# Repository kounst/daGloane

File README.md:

daGloane
========

daGloane is a quadcopter with a takeoff mass of less than 30grams

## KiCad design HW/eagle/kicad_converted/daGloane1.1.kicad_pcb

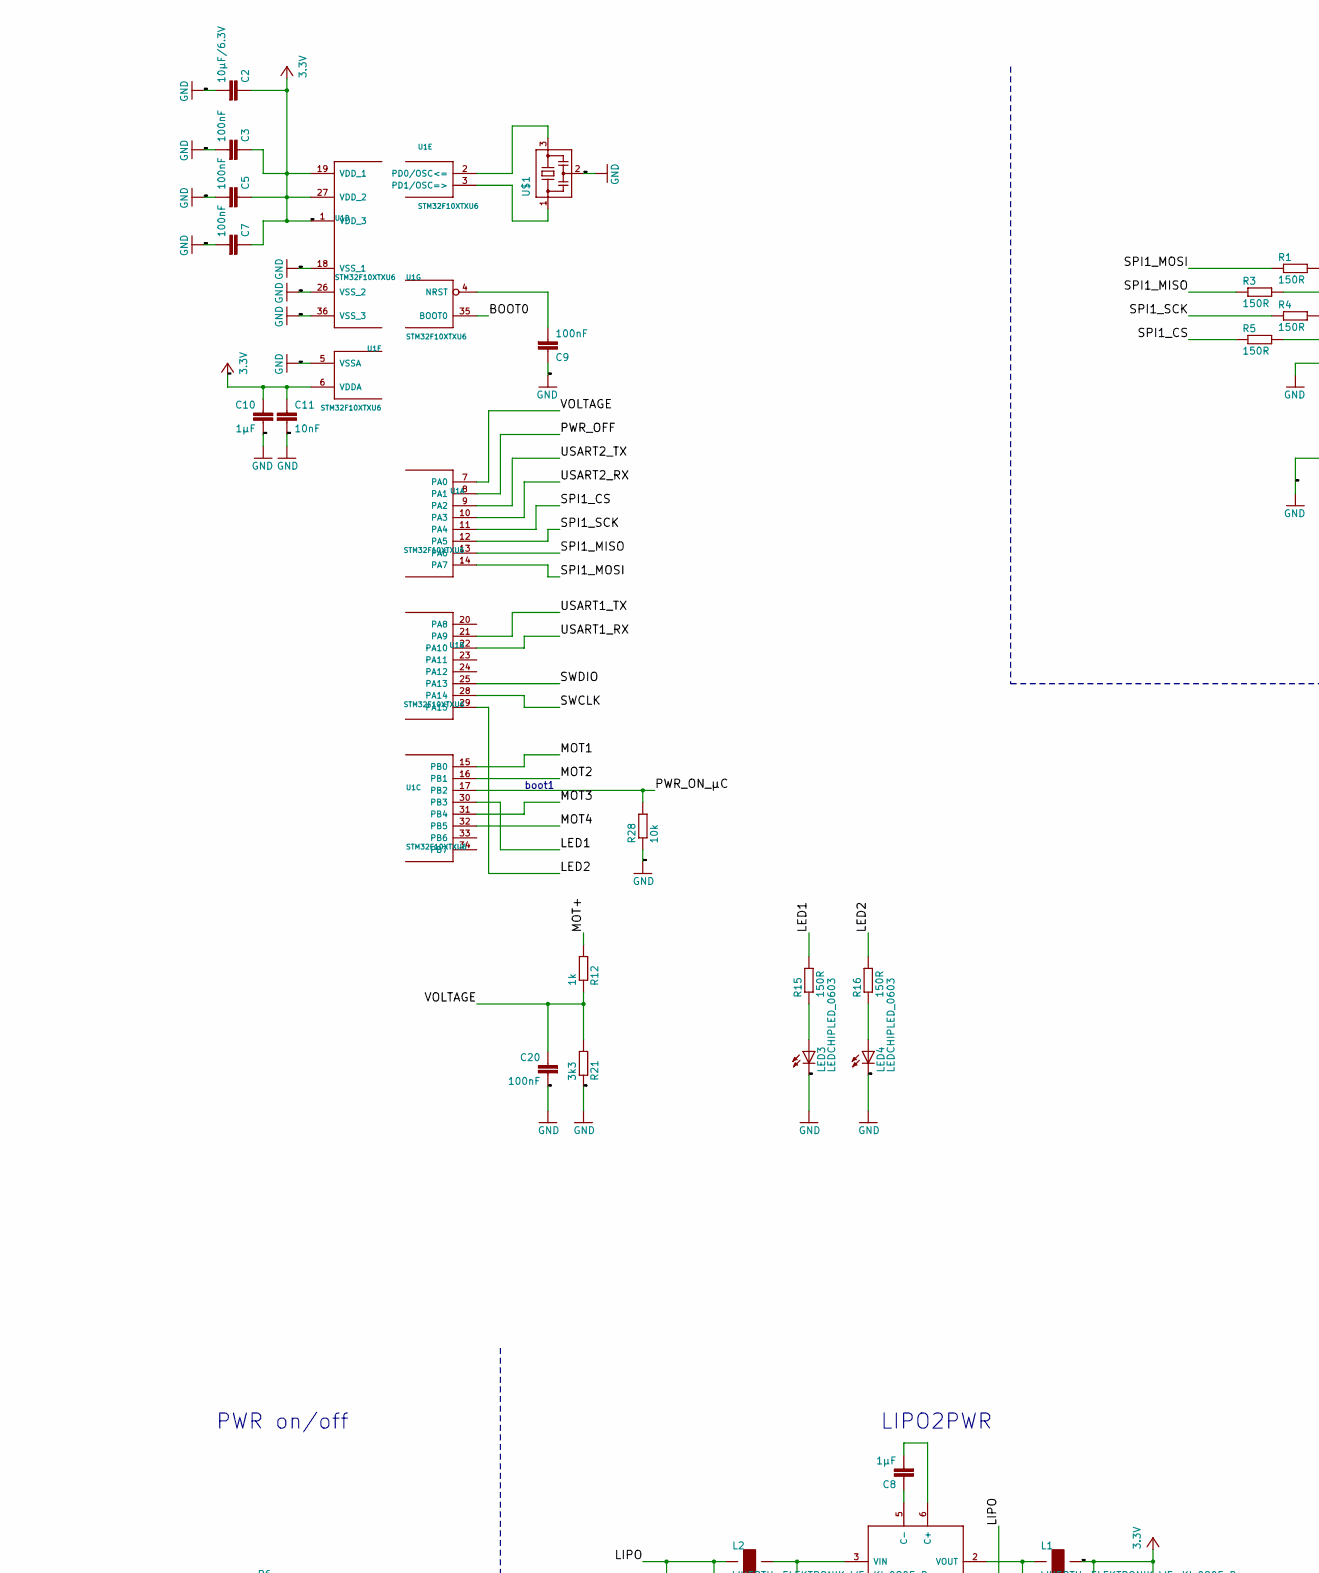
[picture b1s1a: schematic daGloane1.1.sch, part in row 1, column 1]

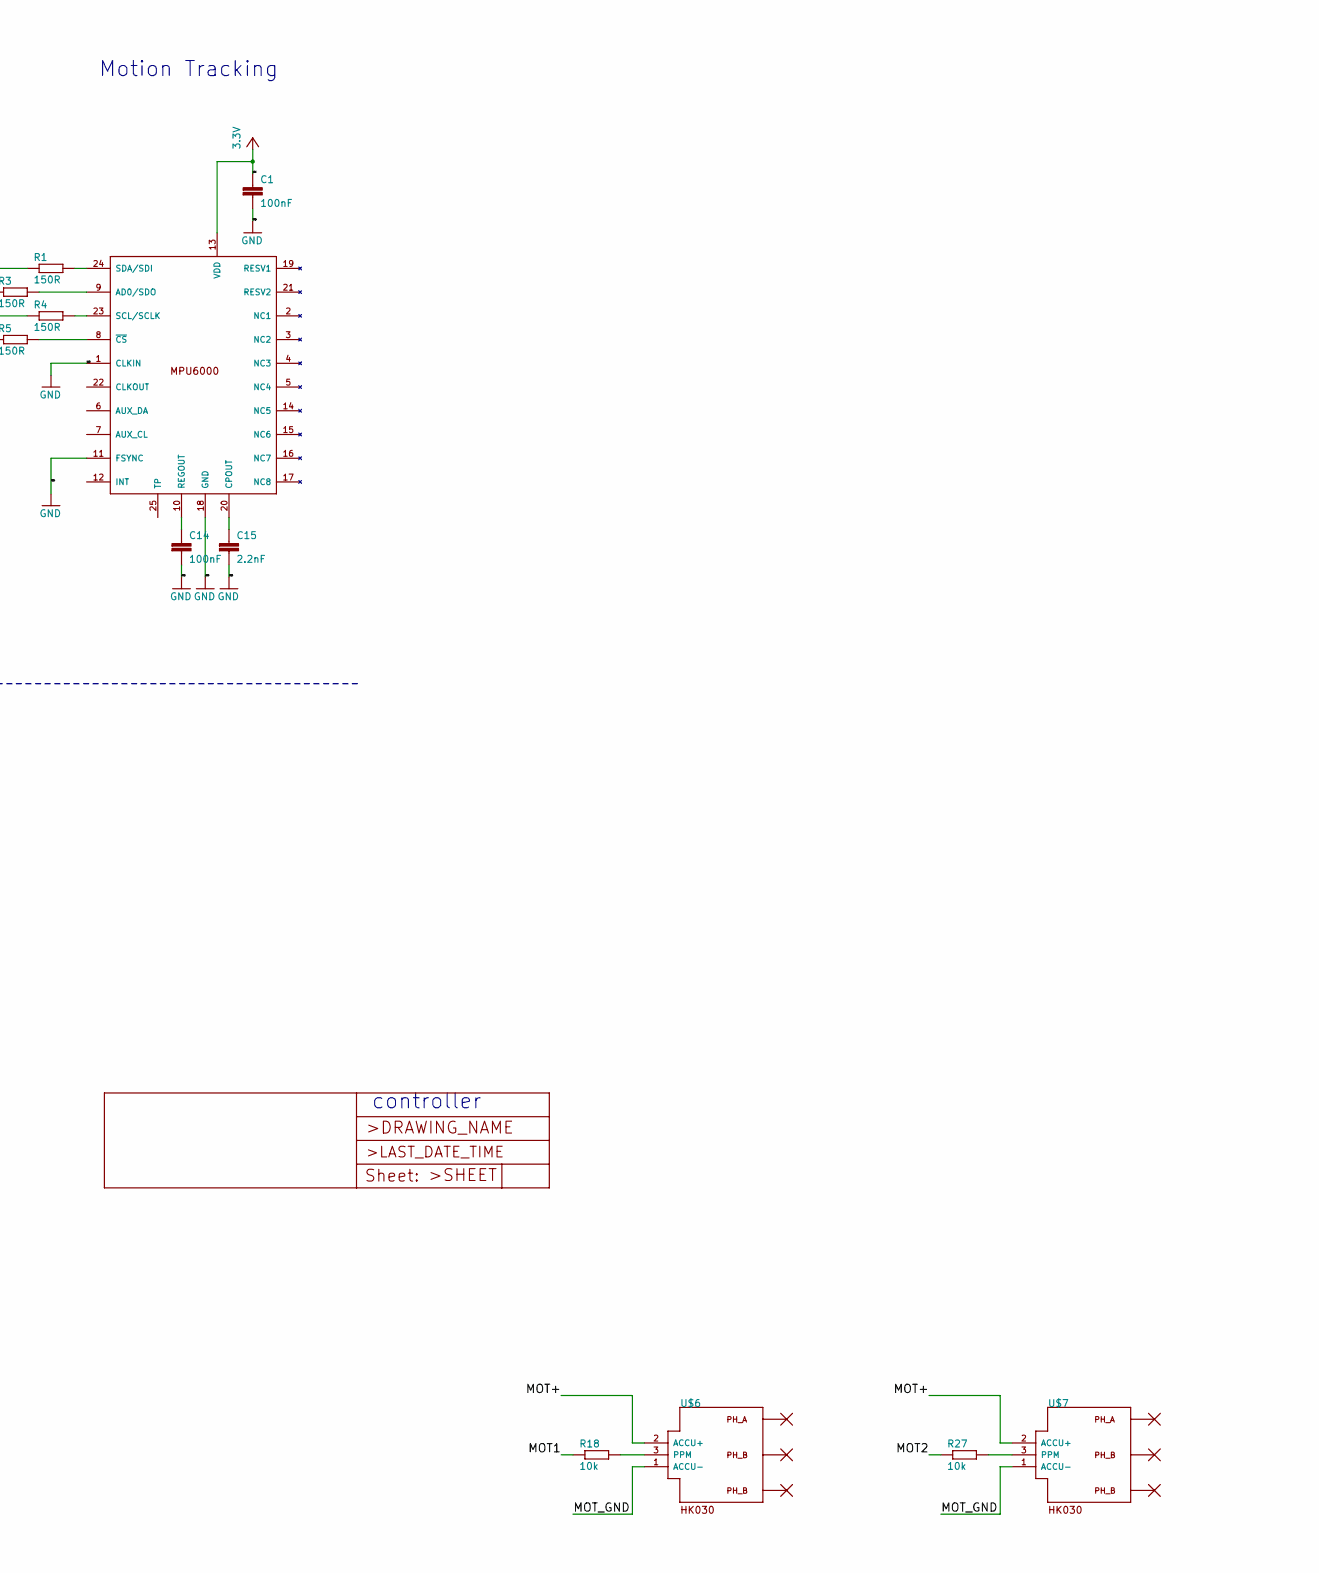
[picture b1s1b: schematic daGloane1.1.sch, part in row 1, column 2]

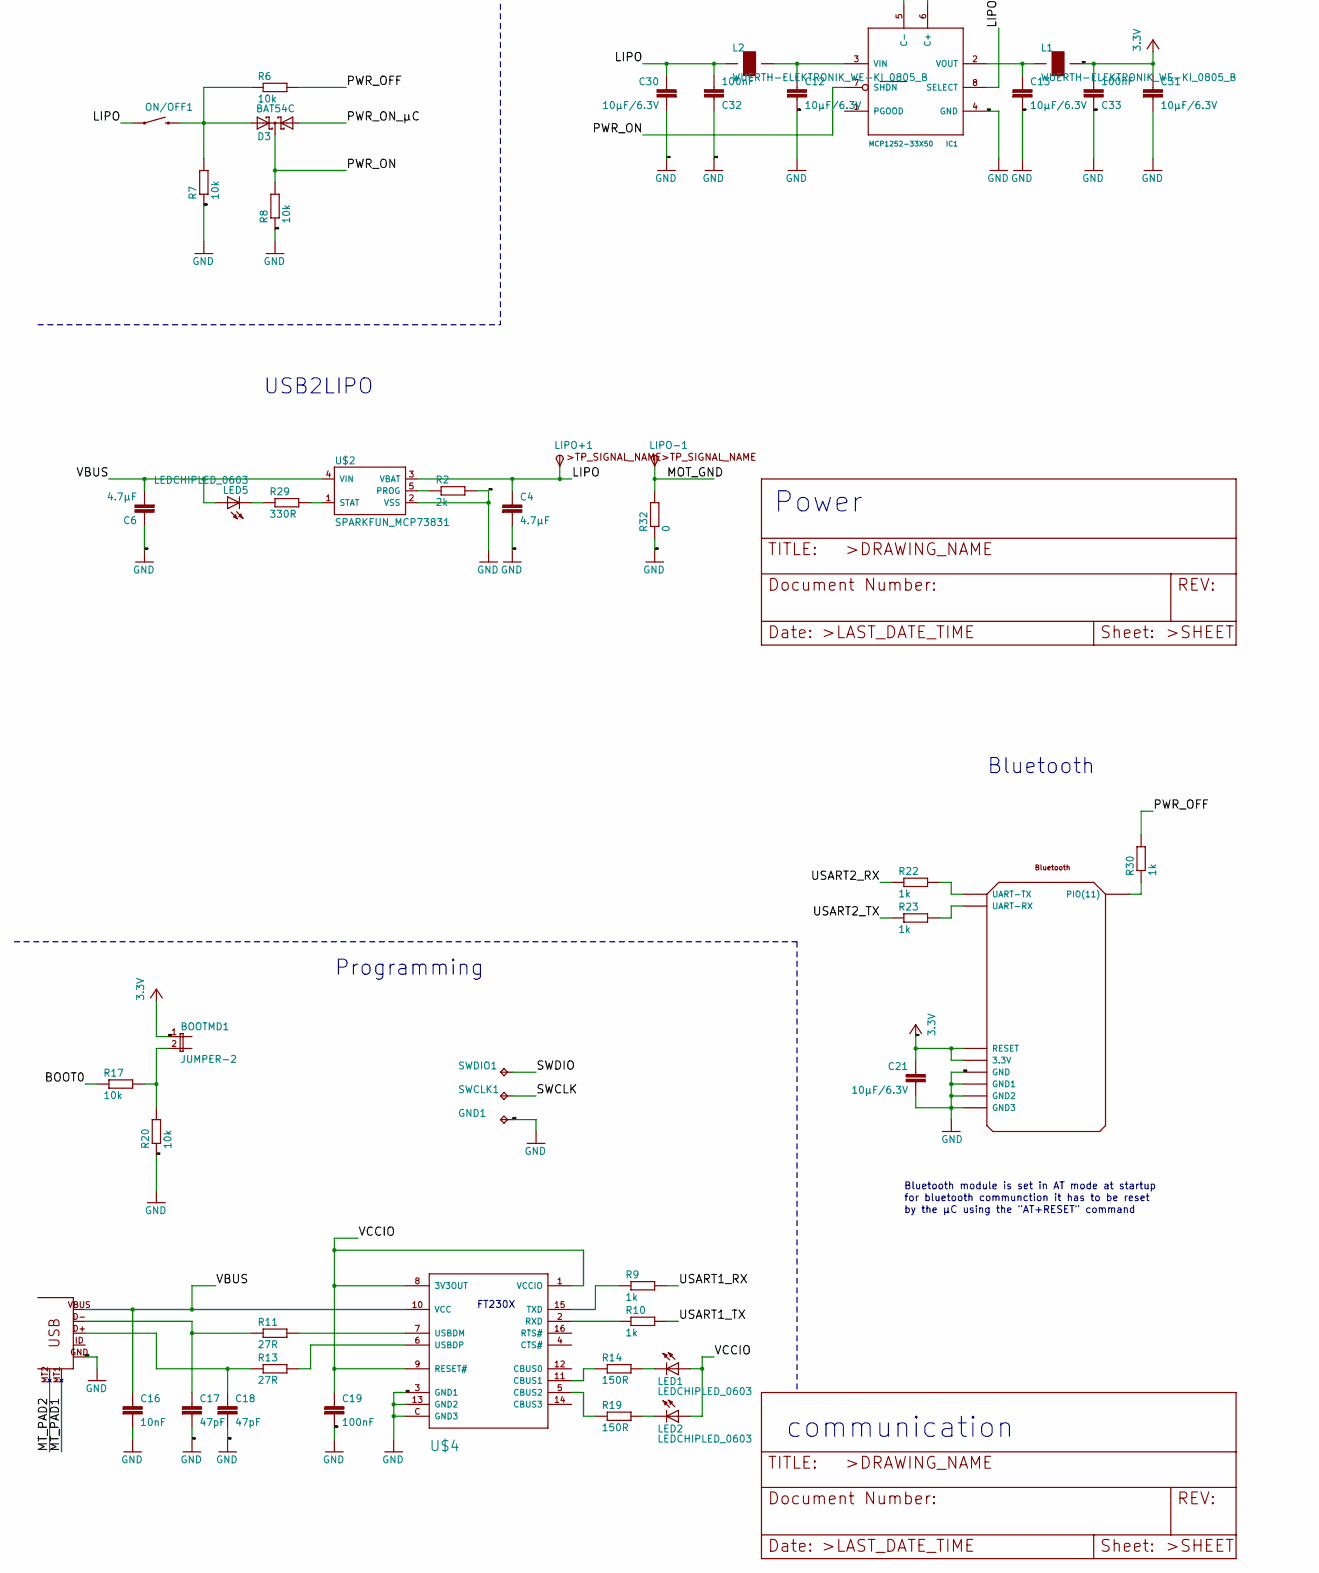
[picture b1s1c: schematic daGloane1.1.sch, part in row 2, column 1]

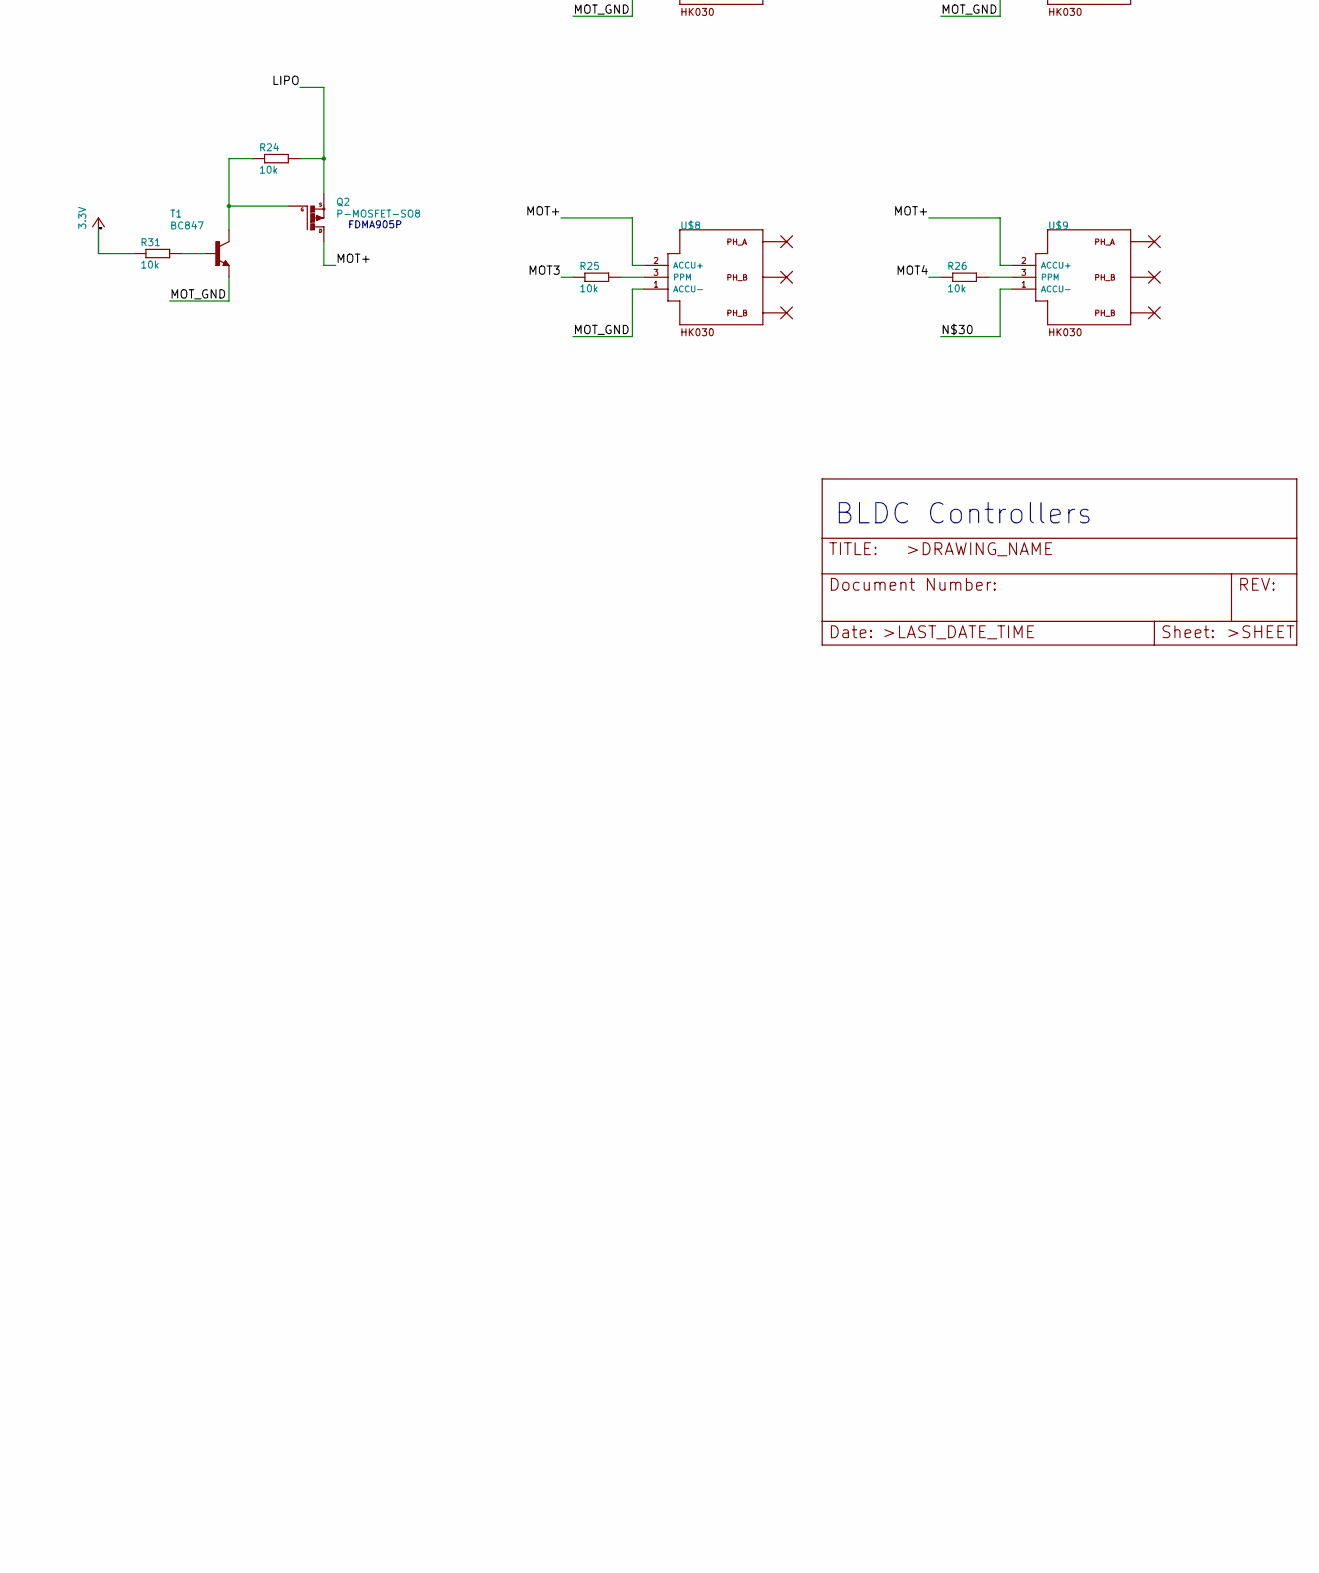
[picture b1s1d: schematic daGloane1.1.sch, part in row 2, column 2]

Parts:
BOOTMD1: JUMPER-2; 1X02_50MIL
C1, C3, C5, C7, C9, C14, C19, C20, C32, C33: 100nF; C0603
C2, C12, C13, C21, C30, C31: 10µF/6.3V; C0805
C4, C6: 4.7µF; C0603
C8, C10: 1µF; C0603
C11, C16: 10nF; C0603
C15: 2.2nF; C0603; VOLTAGE 50V
C17, C18: 47pF; C0603
D3: BAT54C; SOT23
GND1: TESTPAD_TPB1,27; TESTPAD_B1,27
IC1: MCP1252-33X50; MSOP8
L1, L2: WUERTH-ELEKTRONIK_WE-KI_0805_B
LED1, LED2, LED3, LED4, LED5: LEDCHIPLED_0603; CHIPLED_0603
LIPO+1: TPSPAD1-13; P1-13
LIPO-1: TPSPAD1-13; P1-13
ON/OFF1: SWITCH-MOMENTARY-2SMD; TACTILE_SWITCH_SMD
Q2: P-MOSFET-SO8; MICROFET2X2
R1, R3, R4, R5, R14, R15, R16, R19: 150R; R0603
R2: 2k; R0603
R6, R7, R8, R17, R18, R20, R24, R25, R26, R27, R28, R31: 10k; R0603
R9, R10, R12, R22, R23, R30: 1k; R0603
R11, R13: 27R; R0603
R21: 3k3; R0603
R29: 330R; R0603
R32: 0; R0603
SWCLK1: TESTPAD_TPB1,27; TESTPAD_B1,27
SWDIO1: TESTPAD_TPB1,27; TESTPAD_B1,27
T1: BC847; SOT23
U1: STM32F10XTXU6; VFQFPN36
U$1: MURATA-FILTER_CSTCE__G
U$2: SPARKFUN_MCP73831; SPARKFUN_SOT23-5
U$3: MPU6000
U$4: SERIAL_FT230XQ; SERIAL_QFN4X4-16
U$5: BLUETOOTH_REDUCED
U$6, U$7, U$8, U$9: 3A_BLDC_CONTROLLER
X2: USB_MICROB_PLUG_MT; SPARKFUN-CONNECTORS_USB-MICROB

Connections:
/BOOT0: R17.1, U1.35 (BOOT0)
/LED1: R15.2, U1.30 (PB3)
/LED2: R16.2, U1.29 (PA15)
/LIPO: C4.1, C30.1, C32.2, IC1.8 (SELECT), L2.2 (1), LIPO+1.TP, ON/OFF1.1, Q2.P$4 (S), Q2.P$7 (S), R24.2, U$2.3 (VBAT)
/MOT1: R18.1, U1.15 (PB0)
/MOT2: R27.1, U1.16 (PB1)
/MOT3: R25.1, U1.31 (PB4)
/MOT4: R26.1, U1.32 (PB5)
/MOT+: Q2.P$1 (D), Q2.P$2 (D), Q2.P$5 (D), Q2.P$6 (D), Q2.P$8 (D), R12.2, U$6.2 (ACCU+), U$7.2 (ACCU+), U$8.2 (ACCU+), U$9.2 (ACCU+)
/MOT_GND: LIPO-1.TP, R32.2, T1.2 (E), U$6.1 (ACCU-), U$7.1 (ACCU-), U$8.1 (ACCU-)
/MT_PAD1: X2.MT1 (MTN1)
/MT_PAD2: X2.MT2 (MTN2)
/N$30: U$9.1 (ACCU-)
/PWR_OFF: R6.2, R30.2, U1.8 (PA1)
/PWR_ON: D3.3 (CC), IC1.7 (SHDN), R8.2
/PWR_ON_µC: D3.1 (A1), R28.2, U1.17 (PB2)
/SPI1_CS: R5.1, U1.11 (PA4)
/SPI1_MISO: R3.1, U1.13 (PA6)
/SPI1_MOSI: R1.1, U1.14 (PA7)
/SPI1_SCK: R4.1, U1.12 (PA5)
/SWCLK: SWCLK1.PP
/SWDIO: SWDIO1.PP
/USART1_RX: R9.2, U1.22 (PA10)
/USART1_TX: R10.2, U1.21 (PA9)
/USART2_RX: R22.1, U1.10 (PA3)
/USART2_TX: R23.1, U1.9 (PA2)
/VBUS: C6.2, C16.1, LED5.A, U$2.4 (VIN), U$4.10 (VCC), X2.VBUS
/VCCIO: C19.1, LED1.A, LED2.A, U$4.1 (VCCIO), U$4.8 (3V3OUT), U$4.9 (RESET#)
/VOLTAGE: C20.1, R12.1, R21.2, U1.7 (PA0)
GND: C1.2, C2.2, C3.2, C4.2, C5.2, C6.1, C7.2, C9.1, C10.2, C11.2, C12.2, C13.2, C14.2, C15.2, C16.2, C17.2, C18.2, C19.2, C20.2, C21.2, C30.2, C31.2, C32.1, C33.1, GND1.PP, IC1.4 (GND), LED3.C, LED4.C, R2.2, R7.1, R8.1, R20.1, R21.1, R28.1, R32.1, U1.5 (VSSA), U1.18 (VSS_1), U1.26 (VSS_2), U1.36 (VSS_3), U$1.2, U$2.2 (VSS), U$3.1 (CLKIN), U$3.11 (FSYNC), U$3.18 (GND), U$4.3 (GND1), U$4.13 (GND2), U$4.C (GND3), U$5.P$13 (GND), U$5.P$14 (GND1), U$5.P$21 (GND2), U$5.P$22 (GND3), X2.GND
unnamed: BOOTMD1.2, R17.2, R20.2
unnamed: C8.1, IC1.5 (C-)
unnamed: C8.2, IC1.6 (C+)
unnamed: C9.2, U1.4 (NRST)
unnamed: C12.1, IC1.3 (VIN), L2.1 (2)
unnamed: C13.1, IC1.2 (VOUT), L1.2 (1)
unnamed: C14.1, U$3.10 (REGOUT)
unnamed: C15.1, U$3.20 (CPOUT)
unnamed: C17.1, R11.1, X2.D-
unnamed: C18.1, R13.1, X2.D+
unnamed: D3.2 (A2), ON/OFF1.3 (2), R6.1, R7.2
unnamed: LED1.C, R14.2
unnamed: LED2.C, R19.2
unnamed: LED3.A, R15.1
unnamed: LED4.A, R16.1
unnamed: LED5.C, R29.1
unnamed: Q2.P$3 (G), R24.1, T1.3 (C)
unnamed: R1.2, U$3.24 (SDA/SDI)
unnamed: R2.1, U$2.5 (PROG)
unnamed: R3.2, U$3.9 (AD0/SDO)
unnamed: R4.2, U$3.23 (SCL/SCLK)
unnamed: R5.2, U$3.8 (~CS)
unnamed: R9.1, U$4.15 (TXD)
unnamed: R10.1, U$4.2 (RXD)
unnamed: R11.2, U$4.7 (USBDM)
unnamed: R13.2, U$4.6 (USBDP)
unnamed: R14.1, U$4.11 (CBUS1)
unnamed: R18.2, U$6.3 (PPM)
unnamed: R19.1, U$4.5 (CBUS2)
unnamed: R22.2, U$5.P$1 (UART-TX)
unnamed: R23.2, U$5.P$2 (UART-RX)
unnamed: R25.2, U$8.3 (PPM)
unnamed: R26.2, U$9.3 (PPM)
unnamed: R27.2, U$7.3 (PPM)
unnamed: R29.2, U$2.1 (STAT)
unnamed: R30.1, U$5.P$34 (PIO(11))
unnamed: R31.2, T1.1 (B)
unnamed: U1.3 (PD1/OSC=>), U$1.1
unnamed: U1.2 (PD0/OSC<=), U$1.3
VCC: BOOTMD1.1, C1.1, C2.1, C3.1, C5.1, C7.1, C10.1, C11.1, C21.1, C31.1, C33.2, L1.1 (2), R31.1, U1.1 (VDD_3), U1.6 (VDDA), U1.19 (VDD_1), U1.27 (VDD_2), U$3.13 (VDD), U$5.P$11 (RESET), U$5.P$12 (3.3V)

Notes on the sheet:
FT230X
boot1
Power
communication
controller
Programming
Bluetooth
LIPO2PWR
USB2LIPO
PWR on/off
Motion Tracking
BLDC Controllers
Bluetooth module is set in AT mode at startup
for bluetooth communction it has to be reset
by the µC using the "AT+RESET" command
FDMA905P

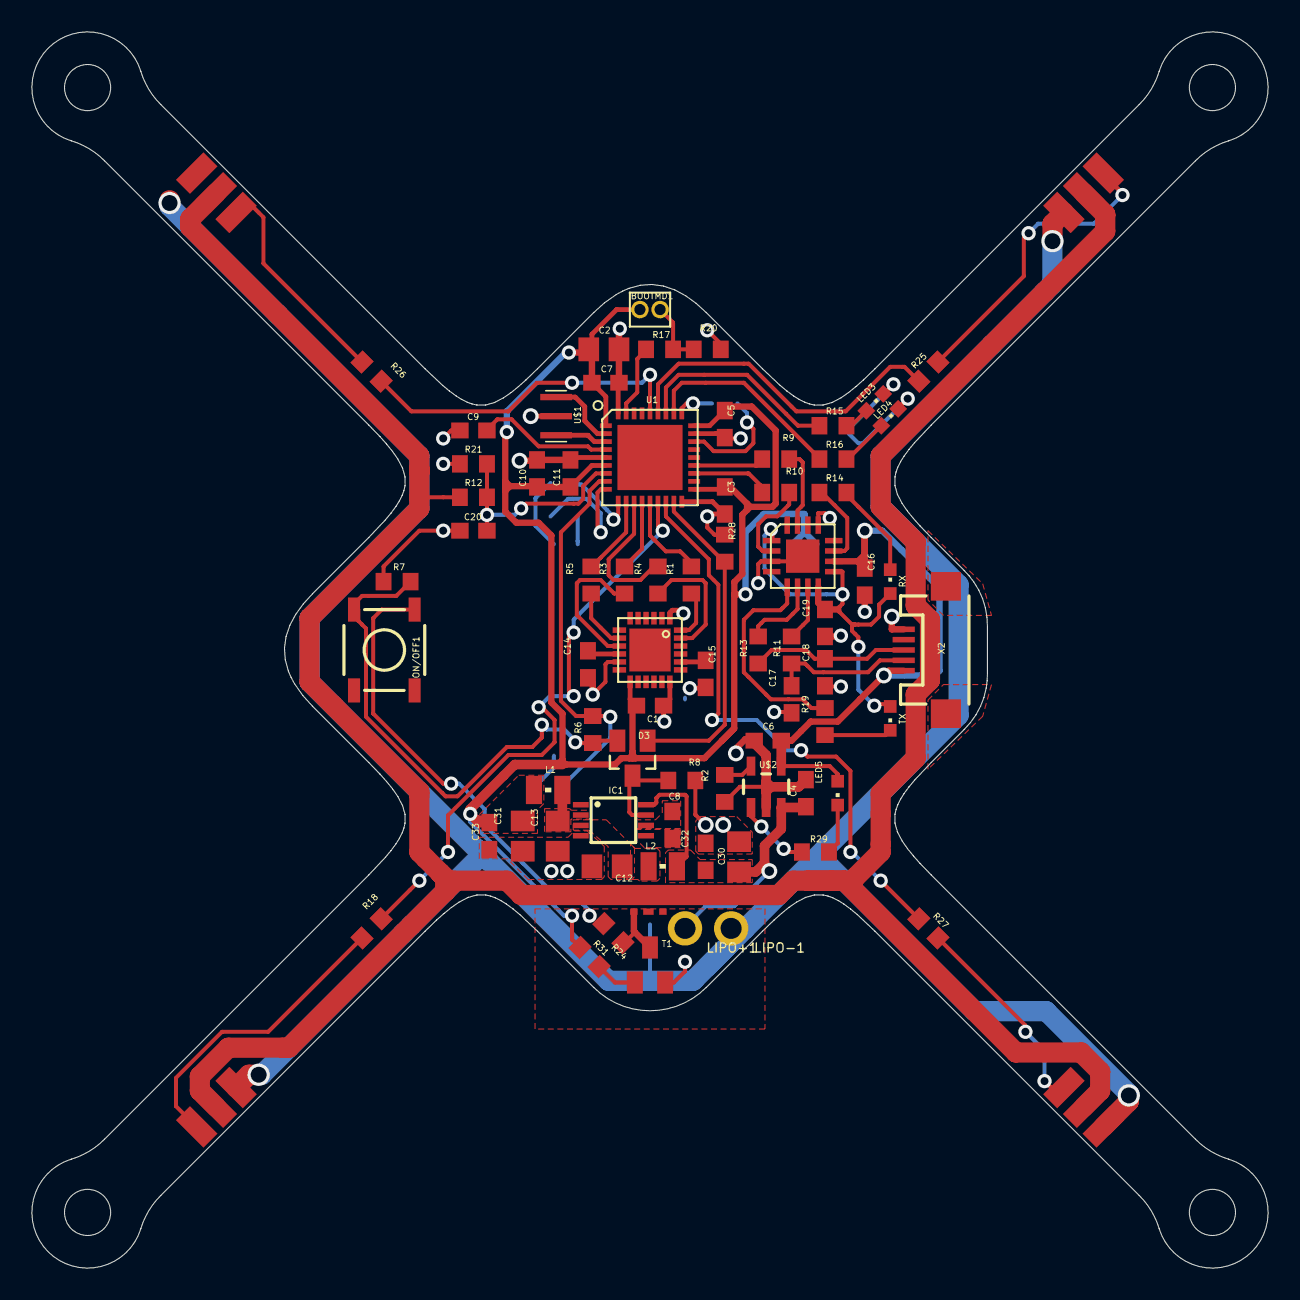
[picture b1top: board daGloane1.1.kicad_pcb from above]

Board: 2 copper layers, 77.7 x 77.7 mm, 91 parts (0 on the bottom side), 65 nets.

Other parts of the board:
@HOLE0, @HOLE1, @HOLE2, @HOLE3: (no value)
U$11: DAGLOANE_LOGO

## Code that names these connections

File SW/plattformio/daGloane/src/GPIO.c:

/*
 * GPIO.c
 *
 *  Created on: Nov 13, 2010
 *      Author: konstantin
 */


/* Includes ------------------------------------------------------------------*/
//#include "stm32f10x.h"
#include "stm32f1xx_hal.h"
#include "GPIO.h"
//#include "uAC.h"


void GPIO_Configuration(void)
{
	GPIO_InitTypeDef GPIO_InitStructure;

	__HAL_AFIO_REMAP_SWJ_NOJTAG();
	__HAL_AFIO_REMAP_TIM3_PARTIAL();
	__HAL_AFIO_REMAP_TIM2_PARTIAL_1();
	// GPIO_PinRemapConfig(GPIO_Remap_SWJ_JTAGDisable, ENABLE);
	// GPIO_PinRemapConfig(GPIO_PartialRemap_TIM3, ENABLE);
	// GPIO_PinRemapConfig(GPIO_PartialRemap1_TIM2, ENABLE);

//   GPIO_InitTypeDef GPIO_InitStruct;
  
//   GPIO_InitStruct.Pin = GPIO_PIN_15;
//   GPIO_InitStruct.Mode = GPIO_MODE_OUTPUT_PP;
//   GPIO_InitStruct.Pull = GPIO_PULLUP;
//   GPIO_InitStruct.Speed = GPIO_SPEED_FREQ_HIGH;
//   HAL_GPIO_Init(GPIOA, &GPIO_InitStruct); 

//   GPIO_InitStruct.Pin = GPIO_PIN_3;
//   HAL_GPIO_Init(GPIOB, &GPIO_InitStruct); 

//   GPIO_InitStruct.Pin = GPIO_PIN_2;
//   HAL_GPIO_Init(GPIOB, &GPIO_InitStruct);   


	/* LED1 & LED2 */
	GPIO_InitStructure.Pin = LED1_PIN;
	//GPIO_InitStructure.GPIO_Mode = GPIO_Mode_AF_PP;
	GPIO_InitStructure.Mode = GPIO_MODE_OUTPUT_PP;
	GPIO_InitStructure.Speed = GPIO_SPEED_FREQ_HIGH;
	HAL_GPIO_Init(LED1_GPIO_PORT, &GPIO_InitStructure);

	GPIO_InitStructure.Pin = LED2_PIN;
	HAL_GPIO_Init(LED2_GPIO_PORT, &GPIO_InitStructure);

//	LEDOff(LED1);
//	LEDOff(LED2);

	/* Power_ON_�C */
	GPIO_InitStructure.Mode = GPIO_MODE_OUTPUT_PP;
	GPIO_InitStructure.Pin = GPIO_PIN_2;
	HAL_GPIO_Init(GPIOB, &GPIO_InitStructure);

	/* Power_OFF */
	GPIO_InitStructure.Pin = GPIO_PIN_1;
	GPIO_InitStructure.Mode = GPIO_MODE_INPUT;
	HAL_GPIO_Init(GPIOA, &GPIO_InitStructure);

	/* MotorPWM 1..4 */
	GPIO_InitStructure.Mode = GPIO_MODE_AF_PP;
	GPIO_InitStructure.Pin = GPIO_PIN_0;
	HAL_GPIO_Init(GPIOB, &GPIO_InitStructure);

	GPIO_InitStructure.Pin = GPIO_PIN_1;
	HAL_GPIO_Init(GPIOB, &GPIO_InitStructure);

	GPIO_InitStructure.Pin = GPIO_PIN_4;
	HAL_GPIO_Init(GPIOB, &GPIO_InitStructure);

	GPIO_InitStructure.Pin = GPIO_PIN_5;
	HAL_GPIO_Init(GPIOB, &GPIO_InitStructure);

	/* SPI Pin Configuration */
	/* SPI_CLK, SPI_MOSI and MISO */
	GPIO_InitStructure.Mode = GPIO_MODE_AF_PP;
	GPIO_InitStructure.Pin = GPIO_PIN_5 | GPIO_PIN_7;
	HAL_GPIO_Init(GPIOA, &GPIO_InitStructure);
	/* SPI_CS */
	GPIO_InitStructure.Mode = GPIO_MODE_OUTPUT_PP;
	GPIO_InitStructure.Pin = GPIO_PIN_4;
	HAL_GPIO_Init(GPIOA, &GPIO_InitStructure);

	GPIO_InitStructure.Mode = GPIO_MODE_INPUT;
	GPIO_InitStructure.Pull = GPIO_PULLDOWN;
	GPIO_InitStructure.Pin = GPIO_PIN_6;
	HAL_GPIO_Init(GPIOA, &GPIO_InitStructure);

	/* Voltage pin PA0 */
	GPIO_InitStructure.Pin = GPIO_PIN_0;
	GPIO_InitStructure.Mode = GPIO_MODE_ANALOG;
	GPIO_InitStructure.Speed = GPIO_SPEED_FREQ_HIGH;
	HAL_GPIO_Init(GPIOA, &GPIO_InitStructure);

	/* Configure USART1 Tx (PA9) as alternate function push-pull */
	GPIO_InitStructure.Pin = GPIO_PIN_9;
	GPIO_InitStructure.Speed = GPIO_SPEED_FREQ_LOW;
	GPIO_InitStructure.Mode = GPIO_MODE_AF_PP;
	HAL_GPIO_Init(GPIOA, &GPIO_InitStructure);

	/* Configure USART1 Rx (PA10) as input floating */
	GPIO_InitStructure.Pin = GPIO_PIN_10;
	GPIO_InitStructure.Pull = GPIO_NOPULL;
	GPIO_InitStructure.Mode = GPIO_MODE_INPUT;
	HAL_GPIO_Init(GPIOA, &GPIO_InitStructure);

	/* Configure USART2 Tx (PA2) as alternate function push-pull */
	GPIO_InitStructure.Pin = GPIO_PIN_2;
	GPIO_InitStructure.Speed = GPIO_SPEED_FREQ_LOW;
	GPIO_InitStructure.Mode = GPIO_MODE_AF_PP;
	HAL_GPIO_Init(GPIOA, &GPIO_InitStructure);

	/* Configure USART2 Rx (PA3) as input floating */
	GPIO_InitStructure.Pin = GPIO_PIN_3;
	GPIO_InitStructure.Pull = GPIO_NOPULL;
	GPIO_InitStructure.Mode = GPIO_MODE_INPUT;
	HAL_GPIO_Init(GPIOA, &GPIO_InitStructure);

}


void PWR_Buttom_handler()
{
	static uint16_t TurnOff_count = 250;

	if(debounce(GPIOA->IDR & 2))		//tactile switch input
	{
		if(TurnOff_count)
		{
			TurnOff_count--;
			if(!(TurnOff_count % 100))
				uac_printf("TurnOff_count: %i\n", TurnOff_count/100);
			if(!TurnOff_count)
				uac_printf("\nBye-bye!\n");
		}
	}
	else
	{
		if(!TurnOff_count)
		{
			GPIOB->BRR = GPIO_PIN_2;	//turn off DCDC
		}
		else
		{
			TurnOff_count = 250;		//reset TurnOff delay
		}
	}
}


/**
 * @brief  Debounces a digital input.
 * @param  IOstate: Specifies the raw input state seen on the input port pin.

 * @retval 0, 1 this is the debounced input state
 */
uint8_t debounce(uint16_t IOstate)
{
	static uint32_t state = 0;
	static uint16_t debounce = 0;

	if(IOstate != 0)
		IOstate = 1;

	state = (state<<1) | IOstate;

	if(state == 0)
		debounce = 0;
	if(state == 0xFFFFFFFF)
		debounce = 1;

	return debounce;
}

/**
 * @brief  Toggles LED1 with 1Hz 50% duty cycle
 * @param  none
 * @retval none
 */
void HeartBeat(void)
{
	static uint16_t heart_count = 0;
	static uint8_t fade_dir = 1;

	if(fade_dir)
		heart_count++;
	else
		heart_count--;

	if(heart_count == 1000)
	{
		fade_dir = 0;
	}
	if(heart_count == 0)
		fade_dir = 1;

	TIM_SetCompare2(TIM2, heart_count*32);

}


const uint16_t GPIO_PIN[2] = {LED1_PIN, LED2_PIN};
GPIO_TypeDef* GPIO_PORT[2] = {LED1_GPIO_PORT, LED2_GPIO_PORT};

/**
 * @brief  Toggles the selected LED.
 * @param  Led: Specifies the Led to be toggled.
 *   This parameter can be one of following parameters:
 *     @arg LED1
 *     @arg LED2
 * @retval None
 */
void LEDToggle(Led_TypeDef Led)
{
	GPIO_PORT[Led]->ODR ^= GPIO_PIN[Led];
}

/**
 * @brief  Turns selected LED On.
 * @param  Led: Specifies the Led to be set on.
 *   This parameter can be one of following parameters:
 *     @arg LED1
 *     @arg LED2
 * @retval None
 */
void LEDOn(Led_TypeDef Led)
{
	GPIO_PORT[Led]->BSRR = GPIO_PIN[Led];
}

/**
 * @brief  Turns selected LED Off.
 * @param  Led: Specifies the Led to be set off.
 *   This parameter can be one of following parameters:
 *     @arg LED1
 *     @arg LED2
 * @retval None
 */
void LEDOff(Led_TypeDef Led)
{
	GPIO_PORT[Led]->BRR = GPIO_PIN[Led];
}

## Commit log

2012-07-07 DC/DC layout done
2012-07-08 layout of center piece is done!
2012-07-08 package added to HK03 BLDC controller library
2012-07-08 testpads replaced with HK03 bldc controller symbol & package
2012-07-08 routing completed!! optimization pending
2012-07-08 orientation of BLDC controllers changed
2012-07-08 GND shape outline changed
2012-07-08 estimation of the total weight of daGloane
2012-07-10 RefDesignators position rearranged
2012-07-11 DC/DC layout improved
2012-07-11 RefDesignator rearranged
2012-07-11 DRC error resolved
2012-07-11 error in schematic fixed: Wrong pin of MPU6000 connected to GND
2012-07-13 Update BLDC
2012-07-15 - micro usb connector with electrical connection to mounting pad added - micro usb connector replaced with new part - micro usb connectors mounting pads' size increased with shape. This is to increas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
2012-07-15 hole diameter for mounting of the motors changed. 2.95mm to 2.90mm
2012-07-15 inital commit of draft "daGloane" logo
2012-07-15 it looks way better now..
2012-07-15 inital commit of logo png
2012-07-15 white filling of ellipses changed to transparent
2012-07-15 resolution increased
2012-07-15 usb connectors added
2012-07-15 image added
2012-07-15 minor change
2012-07-15 reset to previous state
2012-07-16 line width increased
2012-07-19 new perspective logo
2012-07-21 daGloane logo added to library
2012-07-21 logo placed on pcb
2012-07-21 trace angles fixed
2012-07-29 changed connection of the bluetooth module's AT pin.
    It is now connected to the pwr_on/off logic. This will set it into AT mode at startup so the µC can configure the module. Once the configuration is done the µC can set it into operating mode by simpl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
2012-07-29 updated to version in lbr
2012-07-29 removed
2012-07-30 initial commit of BT interface PCB
2012-07-30 labels changed, parts smashed, labels resized and rearranged
2012-07-30 layout finished
2012-07-30 footprint for spring loaded header added
2012-07-31 added status LED
2012-07-31 parts rearranged to leave more space for BT module
2012-07-31 Reference Designators resized rearranged
2012-08-12 bluetooths footprint corrected to actual dimensions
2012-08-12 bluetooth module replaced with new version
2012-08-12 bluetooth module footprint corrected to match actual dimensions
2012-08-12 bluetooth module footprint removed and replaced with dummy drawing
2012-08-12 stm32 vqfpn36 package cream layer divided in 4 segments
2012-08-12 gnd shape slightly changed
2012-08-12 initial commit daGlaone panelized
2012-08-13 changed some values
2012-08-13 resistor values for LEDs changed back; voltage drop over LEDs at 10mA is 2V. Therefore the voltage drop accross the resistor has to be 1.3V (3.3V supply) --> R = 1.3V / 10mA = 130Ohm; next E12 value 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
2012-08-15 initial commit of gerber files
2012-08-17 silkscreen of STM32 and FT230 modified
2012-08-17 silkscreen of stm32 and FT230 modified outline of maximum usable boadspace in eagle freeware version removed
2012-08-18 minor changes
2012-08-20 gerber data for daGlaone and BTinterface
2012-08-20 font type changed to vector
2012-09-16 motor mounting holes diamenters changed to 3.4mm
2012-09-22 initial commit of daGloane firmware. This is code for testing only - no actual functionality
2012-09-22 PWM testcode implemented
2012-10-13 -spi reading from the MPU-6000 is now working (polling mode) -single byte read -continous reading of several bytes - UART command line interface implemented -this was done my using a library by Thoma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
2012-10-13 missing files for SPI and serial command interface (uAC) added string compare function in uAC changed to be case insensitive
2012-10-14 compile switch added to make uac's string compare case insensitive
2012-10-14 unused code removed
2012-10-14 uac message is now sent before daGloane turns itself off
2012-10-14 all data of the MPU-6000 can now be read over the uac interface
2012-10-15 Bit manipulation of data read ofer SPI replaced with union This made it necessary to change the order of high and low byte read from the SPI.
2012-10-20 uAC command handler moved to a seperate file
2012-10-20 header comment changed to look more like the other files comments
2012-10-20 SysTick timer related functions move from main.c to this files
2012-10-20 some functions and prototypes move to other source and header files
2012-10-20 typedef and function prototypes move from main.c to this file
2012-10-20 initial commit of an implementation of the kalman filter. This is completely untested
2012-10-20 we don't really need this..
2012-10-20 printf did't work properly for float smaller than 0 and bigger than -1 This bug fix is untested
2012-10-20 uAC command attach function created
2012-10-20 power button handling moved to seperate funciton in GPIO.c
2012-10-20 missing include of TIM.h added
2012-10-20 #endif statement moved to right location
2012-10-20 several commands moved to seperate functions some comments added
2012-10-23 added TIM.h for Delay function required
2012-10-24 mpu data typedef changed back to previous state
2012-10-25 Remapping of JTAG pins activated. Initialization of LED and PWM3 IOs fixed
2012-10-25 HeartBeat function added
2012-10-25 Heatbeat function added
2012-10-25 this source file implements Consistent Overhead Byte Stuffing. This will be used for the UART communication over the BT module
2012-11-02 prototypes for SPI1_read() and SPI_writebyte() functions added
2012-11-02 SPI1_writebyte() function added
2012-11-02 new uac command added. The command "mpu" allows you to read from or write to a register of the mpu using the command line interface
2012-11-05 disciption of the uart message protocoll to be used by daGloane for communication over BT interface
2012-11-07 PWM update function implemented uac function to set PWM duty-cycle implemented
2012-11-08 heart beat led now fades on and off with a 0.5Hz frequency
2012-11-08 LED fading can be controled with a uac command
2012-11-08 mapping of data in union replaced with function that does bitshifting. This just makes to code way easier to read.
2012-11-11 kalman filter activated for testing
2012-11-11 incorrect mapping of data in MPU_read function fixed
2012-11-11 function for kalman filter tuning implemented
2012-11-17 experimental implementation of bluetooth transmit routines
2012-11-23 scaling of temperatur data provided by mpu-6000 done
2012-11-23 new uac commands: - changing of baudrate uart connected to BT module - sending of data to the BT module
2012-11-23 handler for data received from the BT module implemented
2012-11-23 UART2 enabled for communication with the BT module
2012-11-23 configuration of UART2 for BT communication
2012-11-23 changed length informated that is send along with message to the total number of bytes
2012-11-23 uac command implemented that alows to make the copter send messages over the BT interface
2012-11-25 cobs encoding function added that modifies the input byte array instead of storing the output string to a seperate array
2012-11-25 private function prototypes moved from header to source file calls of alloca function removed
2012-11-25 both LEDs are now turned on in case of an hard fault
2012-11-25 uac command btmsg implementation changed to be more versatile
2012-12-02 New version of daGloane HW. - There is almost no current consumption when turned off. Its not necessary to disconnect battery anymore.
2013-03-10 PWM frequency changed 333Hz 3ms
2013-03-10 help string changed to reflect changes made to PWM
2013-03-10 rotation of gyro signals to prop coordinate system (rotation in z axis by 45 degree) implemented
2013-03-10 code formating; no functional change
2013-03-16 order of channels in BT_message mapping to local variable corrected
2013-03-16 uac command for reading back the pwm values implemented
2013-03-16 bytes that are received via bluetooth are no longer transfered over the uac debugging interface
2013-03-16 gyro data are no longer transmitted via bluetooth interface on uart 2
2013-03-16 initial commit of the daGloane Remote
    The target is to make the daGloane qaudcopter controlable using a Android Smartphone.
    For now to ease devolempent a common RC remote control will be used.
    daGloane Remote is a stm32 discovery eval board and a bluetooth interface that can be connected to a RC remote control. It will read the PPM signal of the remote and transfer the channel information 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
2013-03-16 what is daGloane_remote
2013-03-17 AT communication is now handled in a FSM
2013-09-06 comment changed to make a difference
2013-09-09 Controller and Filter in Simulink. Looking for building a C model via Matlab
2013-09-10 simulink modell
2013-09-10 Erste Version des auf C konvertierten Simulink Codes
2013-09-16 correct signal names discrete int and derivate new c code generated
2013-09-16 new version
2013-09-16 model version 1.14
2013-09-16 initial commit of the daGloane Android remote app
2013-09-16 daGloane fw project zip
2013-09-19 project workspace zip
2013-09-23 software from 23.09.2013. problem in main.c while loop. seems like looping only one time/or 0.
2013-10-06 data collected testing the complementary filter
2013-10-08 neue dateien
2013-10-08 Systick clock frequency changed to 250Hz
2013-10-08 uac command "getpwm" now returns the Motor pwm instead of the remote control pwm signals
2013-10-08 functions for uart dma data transfer added
2013-10-08 tigger flag for main loop execution added; this flag is set in the systick interrupt and is reset in the main loop
2013-10-08 main loop is only being executed if the tigger flag is set; the trigger flag is set by the systick interrupt which is fired at a rate of 250Hz
2013-10-22 22.10. new C Code from simulink model
2013-10-22 for quad model
2013-11-12 new c code
2013-11-14 pid values can now be changed via bluetooth
2021-02-15 step file of pcb added
2021-02-17 Programming fixture added
2021-02-18 Programming fixture improved
2021-02-20 migration of copter FW platformio started
2021-03-01 migration to platfromio and STM32Cube libraries made
2021-03-01 unneded files removed
2021-03-01 kicad converted eagle project added
2021-03-05 complementary filter implementation started
2021-03-14 MPU read is triggered by TIM2 update interrupt now. Main loop runs after SPI communication is done.
